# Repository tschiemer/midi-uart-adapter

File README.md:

# midi-uart-adapter

PCB layout for a simple MIDI (In-Through-Out) / UART - Adapter according to MIDI 1.0 Specification

Does not directly include footprints for MIDI or TRS plugs but rather provides headers such as to more easily allow customization.

Also allows to use different voltage levels for RX, TX respectively (please use different resistors according to recommendations).

https://github.com/tschiemer/midi-uart-adapter

According to simple table-top tests using a Behringer BCF2000 all three connections (in, through, out) work as expected.

## Parts

- [LITEON 6N138](https://datasheet.octopart.com/6N139-Lite-On-datasheet-8327661.pdf) or [ONSEMI 6N138](https://www.onsemi.com/pub/Collateral/HCPL2731-D.PDF) Octocoupler
- [ONSEMI 1N914](https://www.onsemi.com/pub/Collateral/1N914-D.PDF) Laser Diode
- Resistors (RA, RB, RC, RD, RE, RF) when Vrx = Vtx = 5V: 220 Ohm 5% 0.25W, Package 1206 (3216 Metric) (ex. [ Bourns Inc. CR1206-FX-2200ELF](https://www.bourns.com/docs/product-datasheets/CRxxxxx.pdf) )
- *Optional* Ferrite Beads (FB1-6), 1kOhm @ 1MHz, Package 0603 (1608 Metric) (ex. [TDK Corporation MMZ1608Y102BTA00](https://product.tdk.com/en/search/emc/emc/beads/info/print_pdf)), bridge if not used
- *Optional* ~~Capacitor (C1), 0.1UF, Package 0201 (0603 Metric) (ex. [Murata Electronics GRM033C80J104KE15D](https://search.murata.co.jp/Ceramy/image/img/A01X/G101/ENG/GRM033C80J104KE15-01A.pdf)), leave unconnected if not used (works, but too *tiny* package size to solder by hand; well, it's possible ;) )~~
- *Optional* Capacitor (C1), 0.1UF, Package 0603 (1608 Metric) (ex. [KEMET C0603C104K4RACTU](https://www.digikey.com/product-detail/en/kemet/C0603C104K4RACTU/399-1096-1-ND/411371)), leave unconnected if not used

The optional parts (ferrite beads and capacitor) are intended to surpress EMI etc.

## Connections

### H1 (Header 1)

| Pin | Description |
|---|---|
| Vrx | Receiver voltage (standard: +5V) |
| Vtx | Transmitter voltage (standard: +5V) |
| G | Ground |
| Rx | UART RX* |
| Tx | UART TX* |

*According to standard: 31.25 (+/- 1%) Kbaud, asynchronous, with a start bit, 8 data bits (D0 to D7), and a stop bit

*Note* if you are using different voltages than 5V (ie 3.3V) you need other resistor values. Also see electrical specs for suggestion.

### Midi-In/-Through/-Out

| DIN-5pole 180deg Pin* | TRS Connector |
|---|---|
| 2 | T |
| 4 | R |
| 5 | S |

*Pins 1 and 3 are not connected.

## Changelog

v2.1
- Reduced size to fit into 4x5cm
- Added license on silkscreen

v2.0
- Removed unnecessary header pins
- More compact / smaller board size

## References

- [MIDI Electrical Specification Update [2014]](https://www.midi.org/downloads?task=callelement&format=raw&item_id=100&element=f85c494b-2b32-4109-b8c1-083cca2b7db6&method=download)
- [Specification for Use of "TRS" Connectors with MIDI Devices](https://www.midi.org/downloads?task=callelement&format=raw&item_id=171&element=f85c494b-2b32-4109-b8c1-083cca2b7db6&method=download)

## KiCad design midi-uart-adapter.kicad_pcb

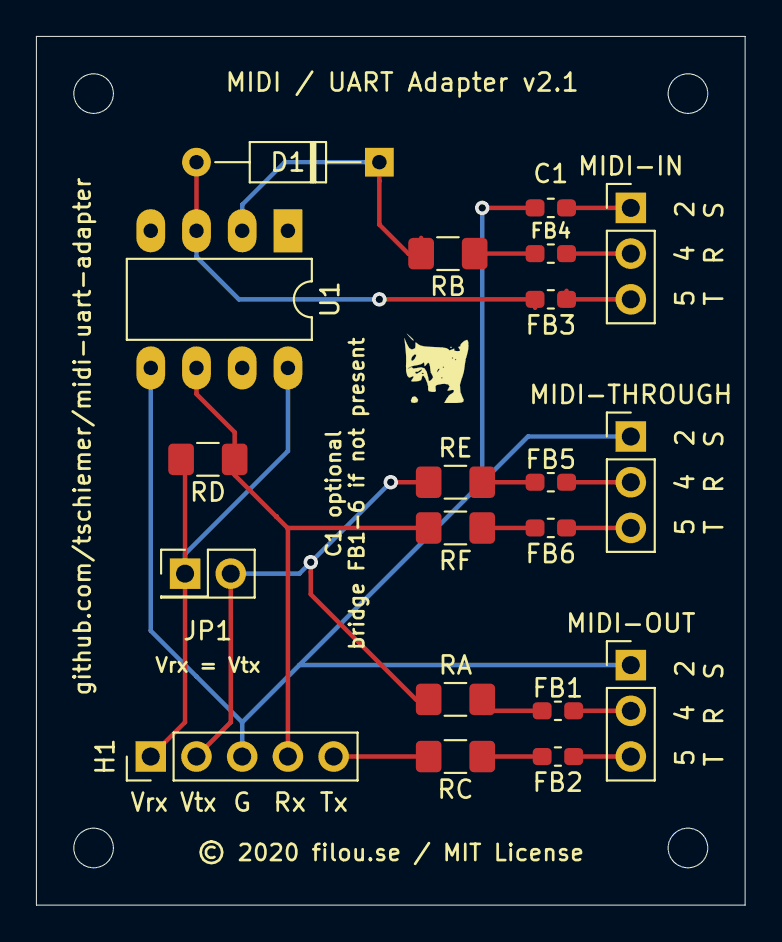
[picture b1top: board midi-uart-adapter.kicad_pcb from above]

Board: 2 copper layers, 39.4 x 48.3 mm, 20 parts (0 on the bottom side), 19 nets.

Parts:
C1: 1 microF; C_0603_1608Metric_Pad1.05x0.95mm_HandSolder
D1: 1N914; D_DO-35_SOD27_P10.16mm_Horizontal
FB1, FB2, FB3, FB4, FB5, FB6: MMZ1608Y102BTA00; R_0603_1608Metric_Pad1.05x0.95mm_HandSolder
H1: Conn_01x05; PinHeader_1x05_P2.54mm_Vertical
JP1: VCC_rx - VCC_tx; PinHeader_2x01_P2.54mm_Vertical
MIDI-IN: Conn_01x05; PinHeader_1x03_P2.54mm_Vertical
MIDI-OUT: Conn_01x05; PinHeader_1x03_P2.54mm_Vertical
MIDI-THROUGH: Conn_01x05; PinHeader_1x03_P2.54mm_Vertical
RA: 220 5% 0.25W; R_1206_3216Metric_Pad1.42x1.75mm_HandSolder
RB: 220 5% 0.25W; R_1206_3216Metric_Pad1.42x1.75mm_HandSolder
RC: 220 5% 0.25W; R_1206_3216Metric_Pad1.42x1.75mm_HandSolder
RD: 220 5% 0.25W; R_1206_3216Metric_Pad1.42x1.75mm_HandSolder
RE: 220 5% 0.25W; R_1206_3216Metric_Pad1.42x1.75mm_HandSolder
RF: 220 5% 0.25W; R_1206_3216Metric_Pad1.42x1.75mm_HandSolder
U1: 6N138; DIP-8_W7.62mm_LongPads

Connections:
GNDREF: C1.2, H1.3, MIDI-OUT.1, MIDI-THROUGH.1, U1.5
unnamed: C1.1, MIDI-IN.1
unnamed: D1.1, RB.2, U1.2
unnamed: D1.2, FB3.2, U1.3
unnamed: FB1.1, MIDI-OUT.2
unnamed: FB1.2, RA.1
unnamed: FB2.1, MIDI-OUT.3
unnamed: FB2.2, RC.1
unnamed: FB3.1, MIDI-IN.3
unnamed: FB4.1, MIDI-IN.2
unnamed: FB4.2, RB.1
unnamed: FB5.1, MIDI-THROUGH.2
unnamed: FB5.2, RE.1
unnamed: FB6.1, MIDI-THROUGH.3
unnamed: FB6.2, RF.1
UART_rx: H1.4, RD.1, RF.2, U1.6
UART_tx: H1.5, RC.2
VCC_rx: H1.1, JP1.1, RD.2, U1.8
VCC_tx: H1.2, JP1.2, RA.2, RE.2

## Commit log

2020-05-31 first hw commit
2020-05-31 readme update
2020-05-31 C2 -> C1 fix, dimensions
2020-05-31 added dimensions to image
2020-05-31 C2 -> C1
2020-05-31 added pdf schematics file
2020-06-04 v2.0
2020-06-05 v2.1
2020-06-05 added connection explanation
2020-06-05 UART settings
2020-07-02 post-test readme update

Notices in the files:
midi-uart-adapter.kicad_pcb:
© 2020 filou.se / MIT License
